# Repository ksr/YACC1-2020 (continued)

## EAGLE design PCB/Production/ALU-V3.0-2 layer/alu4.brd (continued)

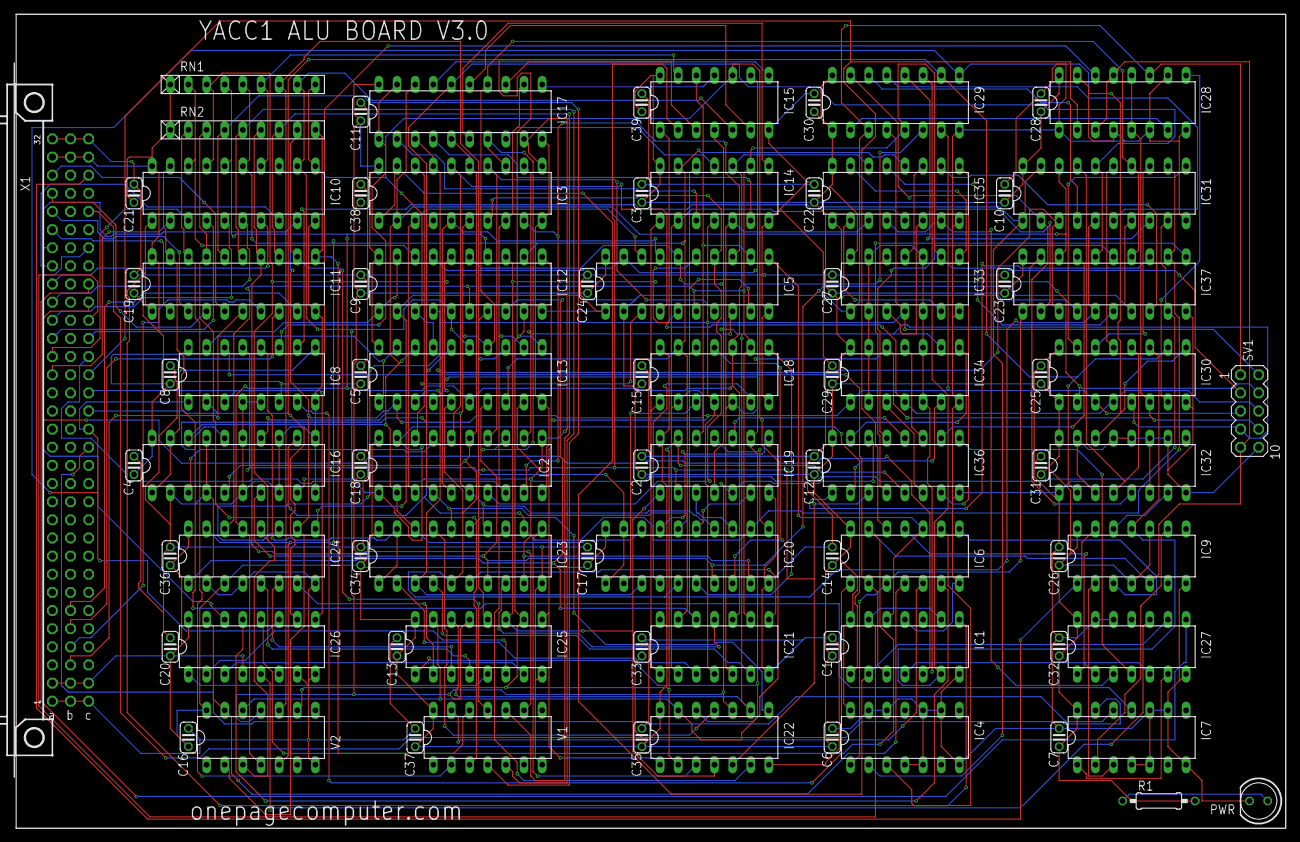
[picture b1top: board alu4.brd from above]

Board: 2 copper layers, 177.8 x 114.0 mm, 84 parts (0 on the bottom side), 158 nets.

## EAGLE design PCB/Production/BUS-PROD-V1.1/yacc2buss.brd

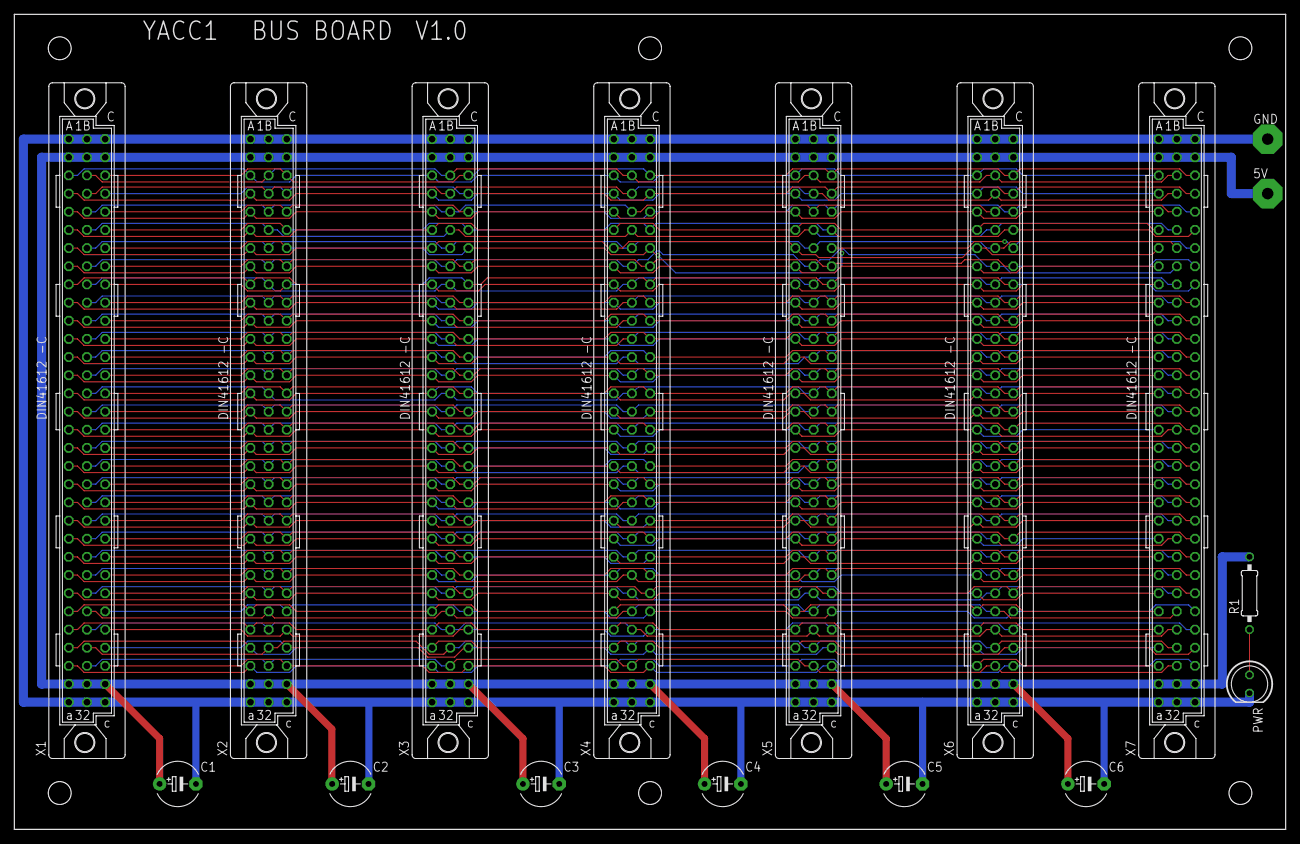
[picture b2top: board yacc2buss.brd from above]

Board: 2 copper layers, 177.8 x 114.0 mm, 17 parts (0 on the bottom side), 87 nets.

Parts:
5V: WIREPAD4,16O1,6; 4,16O1,6
C1, C2, C3, C4, C5, C6: E5-6
GND: WIREPAD4,16O1,6; 4,16O1,6
PWR: LED5MM
R1: 330; 0207/10
X1, X2, X3, X4, X5, X6, X7: FABC96S

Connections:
5V: 5V.1, C1.+, C2.+, C3.+, C4.+, C5.+, C6.+, R1.2, X1.A2, X1.A31, X1.B2, X1.B31, X1.C2, X1.C31, X2.A2, X2.A31, X2.B2, X2.B31, X2.C2, X2.C31, X3.A2, X3.A31, X3.B2, X3.B31, X3.C2, X3.C31, X4.A2, X4.A31, X4.B2, X4.B31, X4.C2, X4.C31, X5.A2, X5.A31, X5.B2, X5.B31, X5.C2, X5.C31, X6.A2, X6.A31, X6.B2, X6.B31, X6.C2, X6.C31, X7.A2, X7.A31, X7.B2, X7.B31, X7.C2, X7.C31
GND: C1.-, C2.-, C3.-, C4.-, C5.-, C6.-, GND.1, PWR.K, X1.A1, X1.A32, X1.B1, X1.B32, X1.C1, X1.C32, X2.A1, X2.A32, X2.B1, X2.B32, X2.C1, X2.C32, X3.A1, X3.A32, X3.B1, X3.B32, X3.C1, X3.C32, X4.A1, X4.A32, X4.B1, X4.B32, X4.C1, X4.C32, X5.A1, X5.A32, X5.B1, X5.B32, X5.C1, X5.C32, X6.A1, X6.A32, X6.B1, X6.B32, X6.C1, X6.C32, X7.A1, X7.A32, X7.B1, X7.B32, X7.C1, X7.C32
unnamed: PWR.A, R1.1
SIG0: X1.A4, X2.A4, X3.A4, X4.A4, X5.A4, X6.A4, X7.A4
SIG1: X1.B4, X2.B4, X3.B4, X4.B4, X5.B4, X6.B4, X7.B4
SIG2: X1.C4, X2.C4, X3.C4, X4.C4, X5.C4, X6.C4, X7.C4
SIG3: X1.A5, X2.A5, X3.A5, X4.A5, X5.A5, X6.A5, X7.A5
SIG4: X1.B5, X2.B5, X3.B5, X4.B5, X5.B5, X6.B5, X7.B5
SIG5: X1.C5, X2.C5, X3.C5, X4.C5, X5.C5, X6.C5, X7.C5
SIG6: X1.A6, X2.A6, X3.A6, X4.A6, X5.A6, X6.A6, X7.A6
SIG7: X1.B6, X2.B6, X3.B6, X4.B6, X5.B6, X6.B6, X7.B6
SIG8: X1.C6, X2.C6, X3.C6, X4.C6, X5.C6, X6.C6, X7.C6
SIG9: X1.A7, X2.A7, X3.A7, X4.A7, X5.A7, X6.A7, X7.A7
SIG10: X1.B7, X2.B7, X3.B7, X4.B7, X5.B7, X6.B7, X7.B7
SIG11: X1.C7, X2.C7, X3.C7, X4.C7, X5.C7, X6.C7, X7.C7
SIG12: X1.A8, X2.A8, X3.A8, X4.A8, X5.A8, X6.A8, X7.A8
SIG13: X1.B8, X2.B8, X3.B8, X4.B8, X5.B8, X6.B8, X7.B8
SIG14: X1.C8, X2.C8, X3.C8, X4.C8, X5.C8, X6.C8, X7.C8
SIG15: X1.A9, X2.A9, X3.A9, X4.A9, X5.A9, X6.A9, X7.A9
SIG16: X1.B9, X2.B9, X3.B9, X4.B9, X5.B9, X6.B9, X7.B9
SIG17: X1.C9, X2.C9, X3.C9, X4.C9, X5.C9, X6.C9, X7.C9
SIG18: X1.A10, X2.A10, X3.A10, X4.A10, X5.A10, X6.A10, X7.A10
SIG19: X1.B10, X2.B10, X3.B10, X4.B10, X5.B10, X6.B10, X7.B10
SIG20: X1.C10, X2.C10, X3.C10, X4.C10, X5.C10, X6.C10, X7.C10
SIG21: X1.A11, X2.A11, X3.A11, X4.A11, X5.A11, X6.A11, X7.A11
SIG22: X1.B11, X2.B11, X3.B11, X4.B11, X5.B11, X6.B11, X7.B11
SIG23: X1.C11, X2.C11, X3.C11, X4.C11, X5.C11, X6.C11, X7.C11
SIG24: X1.A12, X2.A12, X3.A12, X4.A12, X5.A12, X6.A12, X7.A12
SIG25: X1.B12, X2.B12, X3.B12, X4.B12, X5.B12, X6.B12, X7.B12
SIG26: X1.C12, X2.C12, X3.C12, X4.C12, X5.C12, X6.C12, X7.C12
SIG27: X1.A13, X2.A13, X3.A13, X4.A13, X5.A13, X6.A13, X7.A13
SIG28: X1.B13, X2.B13, X3.B13, X4.B13, X5.B13, X6.B13, X7.B13
SIG29: X1.C13, X2.C13, X3.C13, X4.C13, X5.C13, X6.C13, X7.C13
SIG30: X1.A14, X2.A14, X3.A14, X4.A14, X5.A14, X6.A14, X7.A14
SIG31: X1.B14, X2.B14, X3.B14, X4.B14, X5.B14, X6.B14, X7.B14
SIG32: X1.C14, X2.C14, X3.C14, X4.C14, X5.C14, X6.C14, X7.C14
SIG33: X1.A15, X2.A15, X3.A15, X4.A15, X5.A15, X6.A15, X7.A15
SIG34: X1.B15, X2.B15, X3.B15, X4.B15, X5.B15, X6.B15, X7.B15
SIG35: X1.C15, X2.C15, X3.C15, X4.C15, X5.C15, X6.C15, X7.C15
SIG36: X1.A16, X2.A16, X3.A16, X4.A16, X5.A16, X6.A16, X7.A16
SIG37: X1.B16, X2.B16, X3.B16, X4.B16, X5.B16, X6.B16, X7.B16
SIG38: X1.C16, X2.C16, X3.C16, X4.C16, X5.C16, X6.C16, X7.C16
SIG39: X1.A17, X2.A17, X3.A17, X4.A17, X5.A17, X6.A17, X7.A17
SIG40: X1.B17, X2.B17, X3.B17, X4.B17, X5.B17, X6.B17, X7.B17
SIG41: X1.C17, X2.C17, X3.C17, X4.C17, X5.C17, X6.C17, X7.C17
SIG42: X1.A18, X2.A18, X3.A18, X4.A18, X5.A18, X6.A18, X7.A18
SIG43: X1.B18, X2.B18, X3.B18, X4.B18, X5.B18, X6.B18, X7.B18
SIG44: X1.C18, X2.C18, X3.C18, X4.C18, X5.C18, X6.C18, X7.C18
SIG45: X1.A19, X2.A19, X3.A19, X4.A19, X5.A19, X6.A19, X7.A19
SIG46: X1.B19, X2.B19, X3.B19, X4.B19, X5.B19, X6.B19, X7.B19
SIG47: X1.C19, X2.C19, X3.C19, X4.C19, X5.C19, X6.C19, X7.C19
SIG48: X1.A20, X2.A20, X3.A20, X4.A20, X5.A20, X6.A20, X7.A20
SIG49: X1.B20, X2.B20, X3.B20, X4.B20, X5.B20, X6.B20, X7.B20
SIG50: X1.C20, X2.C20, X3.C20, X4.C20, X5.C20, X6.C20, X7.C20
SIG51: X1.A21, X2.A21, X3.A21, X4.A21, X5.A21, X6.A21, X7.A21
SIG52: X1.B21, X2.B21, X3.B21, X4.B21, X5.B21, X6.B21, X7.B21
SIG53: X1.C21, X2.C21, X3.C21, X4.C21, X5.C21, X6.C21, X7.C21
SIG54: X1.A22, X2.A22, X3.A22, X4.A22, X5.A22, X6.A22, X7.A22
SIG55: X1.B22, X2.B22, X3.B22, X4.B22, X5.B22, X6.B22, X7.B22
SIG56: X1.C22, X2.C22, X3.C22, X4.C22, X5.C22, X6.C22, X7.C22
SIG57: X1.A23, X2.A23, X3.A23, X4.A23, X5.A23, X6.A23, X7.A23
SIG58: X1.B23, X2.B23, X3.B23, X4.B23, X5.B23, X6.B23, X7.B23
SIG59: X1.C23, X2.C23, X3.C23, X4.C23, X5.C23, X6.C23, X7.C23
SIG60: X1.A24, X2.A24, X3.A24, X4.A24, X5.A24, X6.A24, X7.A24
SIG61: X1.B24, X2.B24, X3.B24, X4.B24, X5.B24, X6.B24, X7.B24
SIG62: X1.C24, X2.C24, X3.C24, X4.C24, X5.C24, X6.C24, X7.C24
SIG63: X1.A25, X2.A25, X3.A25, X4.A25, X5.A25, X6.A25, X7.A25
SIG64: X1.B25, X2.B25, X3.B25, X4.B25, X5.B25, X6.B25, X7.B25
SIG65: X1.C25, X2.C25, X3.C25, X4.C25, X5.C25, X6.C25, X7.C25
SIG66: X1.A26, X2.A26, X3.A26, X4.A26, X5.A26, X6.A26, X7.A26
SIG67: X1.B26, X2.B26, X3.B26, X4.B26, X5.B26, X6.B26, X7.B26
SIG68: X1.C26, X2.C26, X3.C26, X4.C26, X5.C26, X6.C26, X7.C26
SIG69: X1.A27, X2.A27, X3.A27, X4.A27, X5.A27, X6.A27, X7.A27
SIG70: X1.B27, X2.B27, X3.B27, X4.B27, X5.B27, X6.B27, X7.B27
SIG71: X1.C27, X2.C27, X3.C27, X4.C27, X5.C27, X6.C27, X7.C27
SIG72: X1.A28, X2.A28, X3.A28, X4.A28, X5.A28, X6.A28, X7.A28
SIG73: X1.B28, X2.B28, X3.B28, X4.B28, X5.B28, X6.B28, X7.B28
SIG74: X1.C28, X2.C28, X3.C28, X4.C28, X5.C28, X6.C28, X7.C28
SIG75: X1.A29, X2.A29, X3.A29, X4.A29, X5.A29, X6.A29, X7.A29
SIG76: X1.B29, X2.B29, X3.B29, X4.B29, X5.B29, X6.B29, X7.B29
SIG77: X1.C29, X2.C29, X3.C29, X4.C29, X5.C29, X6.C29, X7.C29
SIG78: X1.A30, X2.A30, X3.A30, X4.A30, X5.A30, X6.A30, X7.A30
SIG79: X1.B30, X2.B30, X3.B30, X4.B30, X5.B30, X6.B30, X7.B30
SIG80: X1.C30, X2.C30, X3.C30, X4.C30, X5.C30, X6.C30, X7.C30
SIG81: X1.A3, X2.A3, X3.A3, X4.A3, X5.A3, X6.A3, X7.A3
SIG82: X1.B3, X2.B3, X3.B3, X4.B3, X5.B3, X6.B3, X7.B3
SIG83: X1.C3, X2.C3, X3.C3, X4.C3, X5.C3, X6.C3, X7.C3

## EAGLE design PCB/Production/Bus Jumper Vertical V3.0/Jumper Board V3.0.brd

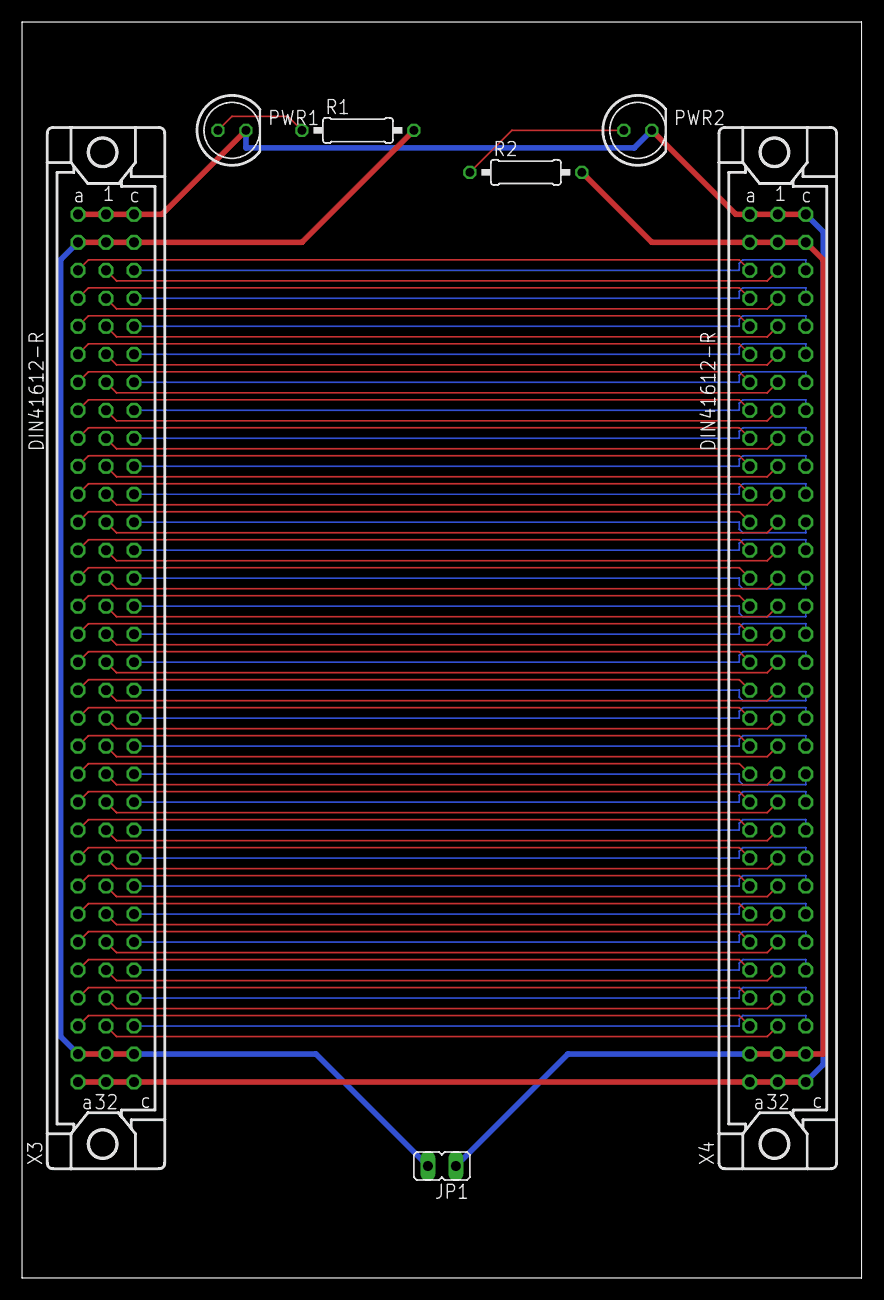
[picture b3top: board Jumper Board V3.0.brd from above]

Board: 2 copper layers, 76.2 x 114.0 mm, 7 parts (0 on the bottom side), 89 nets.

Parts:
JP1: JP1
PWR1, PWR2: LED5MM
R1, R2: 330; 0207/10
X3, X4: MABC96R

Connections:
GND: PWR1.K, PWR2.K, X3.A1, X3.A32, X3.B1, X3.B32, X3.C1, X3.C32, X4.A1, X4.A32, X4.B1, X4.B32, X4.C1, X4.C32
unnamed: X3.A3, X4.A3
unnamed: X3.A4, X4.A4
unnamed: X3.A5, X4.A5
unnamed: X3.A6, X4.A6
unnamed: X3.A7, X4.A7
unnamed: X3.A8, X4.A8
unnamed: X3.A9, X4.A9
unnamed: X3.A10, X4.A10
unnamed: X3.A11, X4.A11
unnamed: X3.A12, X4.A12
unnamed: X3.A13, X4.A13
unnamed: X3.A14, X4.A14
unnamed: X3.A15, X4.A15
unnamed: X3.A16, X4.A16
unnamed: X3.A17, X4.A17
unnamed: X3.A18, X4.A18
unnamed: X3.A19, X4.A19
unnamed: X3.A20, X4.A20
unnamed: X3.A21, X4.A21
unnamed: X3.A22, X4.A22
unnamed: X3.A23, X4.A23
unnamed: X3.A24, X4.A24
unnamed: X3.A25, X4.A25
unnamed: X3.A26, X4.A26
unnamed: X3.A27, X4.A27
unnamed: X3.A28, X4.A28
unnamed: X3.A29, X4.A29
unnamed: X3.A30, X4.A30
unnamed: PWR1.A, R1.1
unnamed: PWR2.A, R2.1
unnamed: X3.B3, X4.B3
unnamed: X3.B4, X4.B4
unnamed: X3.B5, X4.B5
unnamed: X3.B6, X4.B6
unnamed: X3.B7, X4.B7
unnamed: X3.B8, X4.B8
unnamed: X3.B9, X4.B9
unnamed: X3.B10, X4.B10
unnamed: X3.B11, X4.B11
unnamed: X3.B12, X4.B12
unnamed: X3.B13, X4.B13
unnamed: X3.B14, X4.B14
unnamed: X3.B15, X4.B15
unnamed: X3.B16, X4.B16
unnamed: X3.B17, X4.B17
unnamed: X3.B18, X4.B18
unnamed: X3.B19, X4.B19
unnamed: X3.B20, X4.B20
unnamed: X3.B21, X4.B21
unnamed: X3.B22, X4.B22
unnamed: X3.B23, X4.B23
unnamed: X3.B24, X4.B24
unnamed: X3.B25, X4.B25
unnamed: X3.B26, X4.B26
unnamed: X3.B27, X4.B27
unnamed: X3.B28, X4.B28
unnamed: X3.B29, X4.B29
unnamed: X3.B30, X4.B30
unnamed: X3.C3, X4.C3
unnamed: X3.C4, X4.C4
unnamed: X3.C5, X4.C5
unnamed: X3.C6, X4.C6
unnamed: X3.C7, X4.C7
unnamed: X3.C8, X4.C8
unnamed: X3.C9, X4.C9
unnamed: X3.C10, X4.C10
unnamed: X3.C11, X4.C11
unnamed: X3.C12, X4.C12
unnamed: X3.C13, X4.C13
unnamed: X3.C14, X4.C14
unnamed: X3.C15, X4.C15
unnamed: X3.C16, X4.C16
unnamed: X3.C17, X4.C17
unnamed: X3.C18, X4.C18
unnamed: X3.C19, X4.C19
unnamed: X3.C20, X4.C20
unnamed: X3.C21, X4.C21
unnamed: X3.C22, X4.C22
unnamed: X3.C23, X4.C23
unnamed: X3.C24, X4.C24
unnamed: X3.C25, X4.C25
unnamed: X3.C26, X4.C26
unnamed: X3.C27, X4.C27
unnamed: X3.C28, X4.C28
unnamed: X3.C29, X4.C29
unnamed: X3.C30, X4.C30
V1: JP1.2, R1.2, X3.A2, X3.A31, X3.B2, X3.B31, X3.C2, X3.C31
V2: JP1.1, R2.2, X4.A2, X4.A31, X4.B2, X4.B31, X4.C2, X4.C31

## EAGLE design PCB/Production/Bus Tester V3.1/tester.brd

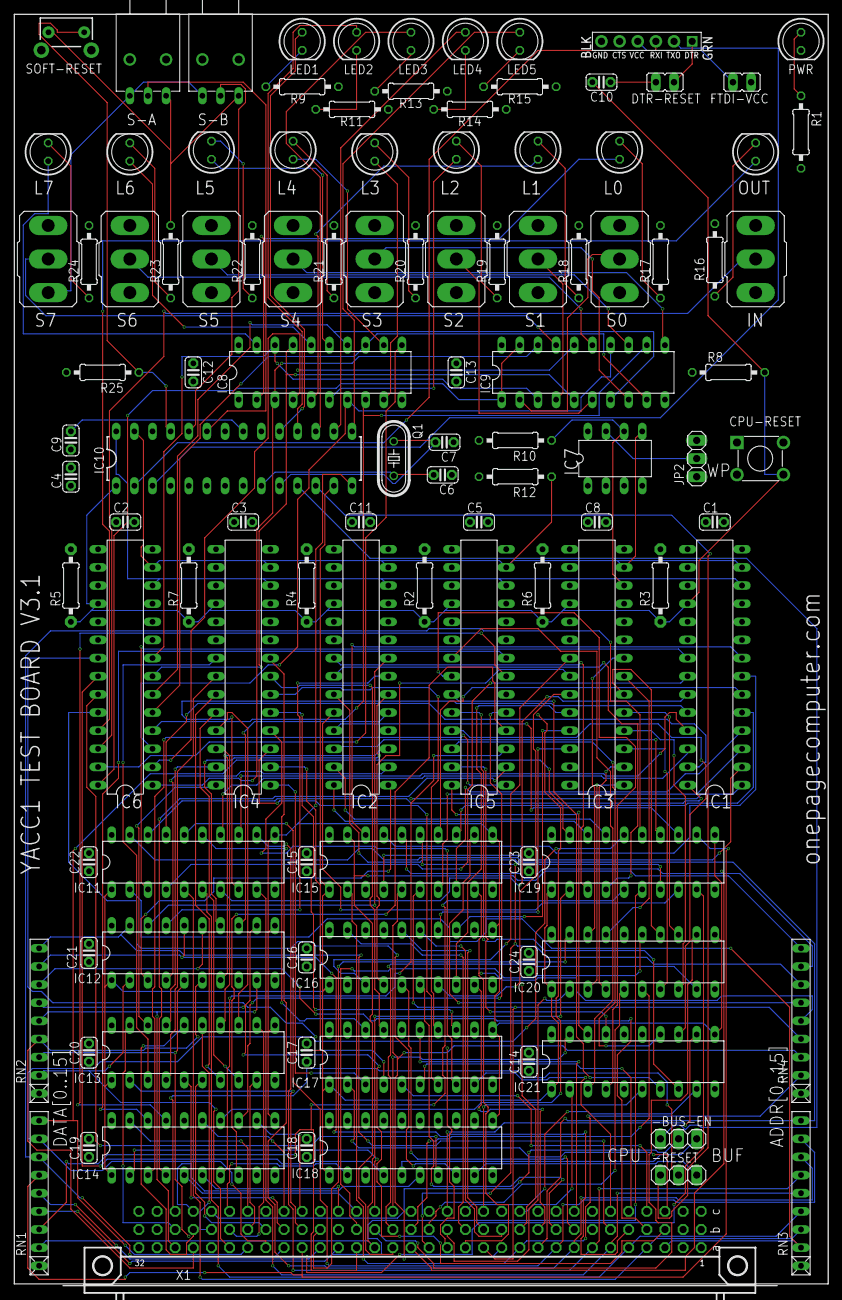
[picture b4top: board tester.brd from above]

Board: 4 copper layers, 114.0 x 177.8 mm, 110 parts (0 on the bottom side), 239 nets.

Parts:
-BUS-EN: 1X03
-RESET: 1X03
C1, C2, C3, C4, C5, C8, C9, C10, C11, C12, C13, C14, C15, C16, C17, C18, C19, C20, C21, C22, C23, C24: 0.1; C025-024X044
C6, C7: 20pf; C025-024X044
CPU-RESET: TS-1109-7; SW4-6.2X6.2X5.0MM
DTR-RESET: JP1
FTDI-VCC: JP1
IC1, IC2, IC3, IC4, IC5, IC6: MCP23017SP; DIL28-3
IC7: 24AA01P; DIL8
IC8: 74LS374N; DIL20
IC9: 74LS244N; DIL20
IC10: ATMEGA328P_PDIP; DIL28-3
IC11, IC12, IC13, IC14, IC15, IC16, IC17, IC18, IC19, IC20, IC21: 74LS373N; DIL20
IN: M9040P
JP1: FTDI_DEVICE; FTDI_DEVICE_SIDE
JP2: 1X03
L0, L1, L2, L3, L4, L5, L6, L7: LED5MM
LED1, LED2, LED3, LED4, LED5: LED5MM
OUT: LED5MM
PWR: LED5MM
Q1: 16Mhz; HC49/S
R1, R9, R11, R13, R14, R15, R16, R17, R18, R19, R20, R21, R22, R23, R24: 330; 0207/10
R2, R3, R4, R5, R6, R7, R8, R25: 10k; 0207/10
R10, R12: 2.2k; 0207/10
RN1, RN2, RN3, RN4: RN-9
S0, S1, S2, S3, S4, S5, S6, S7: M9040P
S-A: 9070-1W
S-B: 9070-1W
SOFT-RESET: SWITCH-MOMENTARY-2SIDE_EZ; TACTILE-PTH-SIDEEZ
X1: FABC96R

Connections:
-BUF-EN: IC10.13, IC11.1, IC12.1, IC13.1, IC14.1, IC15.1, IC16.1, IC17.1, IC18.1, IC19.1, IC20.1, IC21.1
-RESET: C10.2, CPU-RESET.3, IC1.18, IC2.18, IC3.18, IC4.18, IC5.18, IC6.18, IC10.1, R2.1, R3.1, R4.1, R5.1, R6.1, R7.1, R8.2
-SOFT-BUS-EN: -BUS-EN.1, IC10.11
-SOFT-RESET: -RESET.1, IC10.12
A3: IC11.2, RN3.2, X1.A3
A4: IC11.5, RN3.3, X1.A4
A5: IC11.6, RN3.4, X1.A5
A6: IC11.9, RN3.5, X1.A6
A7: IC11.12, RN3.6, X1.A7
A8: IC11.15, RN3.7, X1.A8
A9: IC11.16, RN3.8, X1.A9
A10: IC11.19, RN3.9, X1.A10
A11: IC15.2, RN4.2, X1.A11
A12: IC15.5, RN4.3, X1.A12
A13: IC15.6, RN4.4, X1.A13
A14: IC15.9, RN4.5, X1.A14
A15: IC15.12, RN4.6, X1.A15
A16: IC15.15, RN4.7, X1.A16
A17: IC15.16, RN4.8, X1.A17
A18: IC15.19, RN4.9, X1.A18
A19: IC19.2, RN1.2, X1.A19
A20: IC19.5, RN1.3, X1.A20
A21: IC19.6, RN1.4, X1.A21
A22: IC19.9, RN1.5, X1.A22
A23: IC19.12, RN1.6, X1.A23
A24: IC19.15, RN1.7, X1.A24
A25: IC19.16, RN1.8, X1.A25
A26: IC19.19, RN1.9, X1.A26
A27: IC12.2, RN2.2, X1.A27
A28: IC12.5, RN2.3, X1.A28
A29: IC12.6, RN2.4, X1.A29
A30: IC12.9, RN2.5, X1.A30
ARD-RXIN: IC10.2, JP1.P$3
ARD-TXOUT: IC10.3, JP1.P$2
B3: IC12.12, RN2.6, X1.B3
B4: IC12.15, RN2.7, X1.B4
B5: IC12.16, RN2.8, X1.B5
B6: IC12.19, RN2.9, X1.B6
B7: IC16.2, X1.B7
B8: IC16.5, X1.B8
B9: IC16.6, X1.B9
B10: IC16.9, X1.B10
B11: IC16.12, X1.B11
B12: IC16.15, X1.B12
B13: IC16.16, X1.B13
B14: IC16.19, X1.B14
B15: IC20.2, X1.B15
B16: IC20.5, X1.B16
B17: IC20.6, X1.B17
B18: IC20.9, X1.B18
B19: IC20.12, X1.B19
B20: IC20.15, X1.B20
B21: IC20.16, X1.B21
B22: IC20.19, X1.B22
B23: IC13.2, X1.B23
B24: IC13.5, X1.B24
B25: IC13.6, X1.B25
B26: IC13.9, X1.B26
B27: IC13.12, X1.B27
B28: IC13.15, X1.B28
B29: IC13.16, X1.B29
B30: IC13.19, X1.B30
BIT0: IC6.1, IC8.3, IC9.18
BIT1: IC6.2, IC8.4, IC9.16
BIT2: IC6.3, IC8.7, IC9.14
BIT3: IC6.4, IC8.8, IC9.12
BIT4: IC6.5, IC8.13, IC9.9
BIT5: IC6.6, IC8.14, IC9.7
BIT6: IC6.7, IC8.17, IC9.5
BIT7: IC6.8, IC8.18, IC9.3
BUF-A3: IC1.21, IC11.3
BUF-A4: IC1.22, IC11.4
BUF-A5: IC1.23, IC11.7
BUF-A6: IC1.24, IC11.8
BUF-A7: IC1.25, IC11.13
BUF-A8: IC1.26, IC11.14
BUF-A9: IC1.27, IC11.17
BUF-A10: IC1.28, IC11.18
BUF-A11: IC1.1, IC15.3
BUF-A12: IC1.2, IC15.4
BUF-A13: IC1.3, IC15.7
BUF-A14: IC1.4, IC15.8
BUF-A15: IC1.5, IC15.13
BUF-A16: IC1.6, IC15.14
BUF-A17: IC1.7, IC15.17
BUF-A18: IC1.8, IC15.18
BUF-A19: IC2.21, IC19.3
BUF-A20: IC2.22, IC19.4
BUF-A21: IC2.23, IC19.7
BUF-A22: IC2.24, IC19.8
BUF-A23: IC2.25, IC19.13
BUF-A24: IC2.26, IC19.14
BUF-A25: IC2.27, IC19.17
BUF-A26: IC2.28, IC19.18
BUF-A27: IC2.1, IC12.3
BUF-A28: IC2.2, IC12.4
BUF-A29: IC2.3, IC12.7
BUF-A30: IC2.4, IC12.8
BUF-B3: IC2.5, IC12.13
BUF-B4: IC2.6, IC12.14
BUF-B5: IC2.7, IC12.17
BUF-B6: IC2.8, IC12.18
BUF-B7: IC3.21, IC16.3
BUF-B8: IC3.22, IC16.4
BUF-B9: IC3.23, IC16.7
BUF-B10: IC3.24, IC16.8
BUF-B11: IC3.25, IC16.13
BUF-B12: IC3.26, IC16.14
BUF-B13: IC3.27, IC16.17
BUF-B14: IC3.28, IC16.18
BUF-B15: IC3.1, IC20.3
BUF-B16: IC3.2, IC20.4
BUF-B17: IC3.3, IC20.7
BUF-B18: IC3.4, IC20.8
BUF-B19: IC3.5, IC20.13
BUF-B20: IC3.6, IC20.14
BUF-B21: IC3.7, IC20.17
BUF-B22: IC3.8, IC20.18
BUF-B23: IC4.21, IC13.3
BUF-B24: IC4.22, IC13.4
BUF-B25: IC4.23, IC13.7
BUF-B26: IC4.24, IC13.8
BUF-B27: IC4.25, IC13.13
BUF-B28: IC4.26, IC13.14
BUF-B29: IC4.27, IC13.17
BUF-B30: IC4.28, IC13.18
BUF-C3: IC4.1, IC17.3
BUF-C4: IC4.2, IC17.4
BUF-C5: IC4.3, IC17.7
BUF-C6: IC4.4, IC17.8
BUF-C7: IC4.5, IC17.13
BUF-C8: IC4.6, IC17.14
BUF-C9: IC4.7, IC17.17
BUF-C10: IC4.8, IC17.18
BUF-C11: IC5.21, IC21.3
BUF-C12: IC5.22, IC21.4
BUF-C13: IC5.23, IC21.7
BUF-C14: IC5.24, IC21.8
BUF-C15: IC5.25, IC21.13
BUF-C16: IC5.26, IC21.14
BUF-C17: IC5.27, IC21.17
BUF-C18: IC5.28, IC21.18
BUF-C19: IC5.1, IC14.3
BUF-C20: IC5.2, IC14.4
BUF-C21: IC5.3, IC14.7
BUF-C22: IC5.4, IC14.8
BUF-C23: IC5.5, IC14.13
BUF-C24: IC5.6, IC14.14
BUF-C25: IC5.7, IC14.17
BUF-C26: IC5.8, IC14.18
BUF-C27: IC6.21, IC18.3
BUF-C28: IC6.22, IC18.4
BUF-C29: IC6.23, IC18.7
BUF-C30: IC6.24, IC18.8
BUF-CLK: IC10.14, IC11.11, IC12.11, IC13.11, IC14.11, IC15.11, IC16.11, IC17.11, IC18.11, IC19.11, IC20.11, IC21.11
C3: IC17.2, X1.C3
C4: IC17.5, X1.C4
C5: IC17.6, X1.C5
C6: IC17.9, X1.C6
C7: IC17.12, X1.C7
C8: IC17.15, X1.C8
C9: IC17.16, X1.C9
C10: IC17.19, X1.C10
C11: IC21.2, X1.C11
C12: IC21.5, X1.C12
C13: IC21.6, X1.C13
C14: IC21.9, X1.C14
C15: IC21.12, X1.C15
C16: IC21.15, X1.C16
C17: IC21.16, X1.C17
C18: IC21.19, X1.C18
C19: IC14.2, X1.C19
C20: IC14.5, X1.C20
C21: IC14.6, X1.C21
C22: IC14.9, X1.C22
C23: IC14.12, X1.C23
C24: IC14.15, X1.C24
C25: IC14.16, X1.C25
C26: IC14.19, X1.C26
C27: IC18.2, X1.C27
C28: -BUS-EN.2, X1.C28
C29: IC18.6, X1.C29
C30: -RESET.2, X1.C30
GND: C1.1, C2.1, C3.1, C4.1, C5.1, C6.1, C7.1, C8.1, C9.1, C11.1, C12.1, C13.1, C14.1, C15.1, C16.1, C17.1, C18.1, C19.1, C20.1, C21.1, C22.1, C23.1, C24.1, CPU-RESET.1, IC1.10, IC1.15, IC1.16, IC1.17, IC2.10, IC2.16, IC2.17, IC3.10, IC3.15, IC3.17, IC4.10, IC4.17, IC5.10, IC5.15, IC5.16, IC6.10, IC6.16, IC7.4, IC8.1, IC8.10, IC9.10, IC10.8, IC10.22, IC11.10, IC12.10, IC13.10, IC14.10, IC15.10, IC16.10, IC17.10, IC18.10, IC18.13, IC18.14, IC18.17, IC18.18, IC19.10, IC20.10, IC21.10, IN.3, JP1.P$5, JP1.P$6, JP2.1, PWR.K, R9.2, R11.2, R13.2, R14.2, R15.2, R16.2, R17.2, R18.2, R19.2, R20.2, R21.2, R22.2, R23.2, R24.2, S0.3, S1.3, S2.3, S3.3, S4.3, S5.3, S6.3, S7.3, S-A.3, S-B.3, SOFT-RESET.2, X1.A1, X1.A32, X1.B1, X1.B32, X1.C1, X1.C32
IN-SWITCH: IC6.26, IN.2
LEDS-LD: IC6.27, IC8.11
unnamed: IC10.19, LED1.A
unnamed: IC7.7, JP2.2
unnamed: C6.2, IC10.9, Q1.2
unnamed: C7.2, IC10.10, Q1.1
unnamed: PWR.A, R1.1
unnamed: IC10.18, LED2.A
unnamed: IC10.17, LED3.A
unnamed: IC10.16, LED4.A
unnamed: C10.1, DTR-RESET.2
unnamed: IC10.15, LED5.A
unnamed: LED2.K, R11.1
unnamed: LED1.K, R9.1
unnamed: LED3.K, R13.1
unnamed: C9.2, IC10.21
unnamed: LED4.K, R14.1
unnamed: LED5.K, R15.1
unnamed: L7.K, R24.1
unnamed: IC10.23, S-A.2
unnamed: IC10.24, S-B.2
unnamed: L6.K, R23.1
unnamed: L5.K, R22.1
unnamed: L4.K, R21.1
unnamed: L3.K, R20.1
unnamed: L2.K, R19.1
unnamed: L1.K, R18.1
unnamed: L0.K, R17.1
unnamed: OUT.K, R16.1
unnamed: DTR-RESET.1, JP1.P$1
unnamed: FTDI-VCC.2, JP1.P$4
unnamed: -BUS-EN.3, IC18.5
unnamed: IC8.5, L1.A
unnamed: IC8.9, L3.A
unnamed: IC8.12, L4.A
unnamed: IC8.15, L5.A
unnamed: IC8.6, L2.A
unnamed: IC8.16, L6.A
unnamed: IC8.19, L7.A
unnamed: IC8.2, L0.A
unnamed: IC10.25, R25.1, SOFT-RESET.1
unnamed: IC9.2, S0.2
unnamed: IC9.8, S3.2
unnamed: IC9.6, S2.2
unnamed: IC9.4, S1.2
unnamed: IC9.11, S4.2
unnamed: IC9.17, S7.2
unnamed: IC9.13, S5.2
unnamed: IC9.15, S6.2
unnamed: -RESET.3, IC18.9
OUT-LED: IC6.25, OUT.A
SCL: IC1.12, IC2.12, IC3.12, IC4.12, IC5.12, IC6.12, IC7.6, IC10.28, R10.1
SDA: IC1.13, IC2.13, IC3.13, IC4.13, IC5.13, IC6.13, IC7.5, IC10.27, R12.1
SWITCHES-RD: IC6.28, IC9.1, IC9.19
VCC: C1.2, C2.2, C3.2, C4.2, C5.2, C8.2, C11.2, C12.2, C13.2, C14.2, C15.2, C16.2, C17.2, C18.2, C19.2, C20.2, C21.2, C22.2, C23.2, C24.2, FTDI-VCC.1, IC1.9, IC2.9, IC2.15, IC3.9, IC3.16, IC4.9, IC4.15, IC4.16, IC5.9, IC5.17, IC6.9, IC6.15, IC6.17, IC7.1, IC7.2, IC7.3, IC7.8, IC8.20, IC9.20, IC10.7, IC10.20, IC11.20, IC12.20, IC13.20, IC14.20, IC15.20, IC16.20, IC17.20, IC18.20, IC19.20, IC20.20, IC21.20, IN.1, JP2.3, R1.2, R2.2, R3.2, R4.2, R5.2, R6.2, R7.2, R8.1, R10.2, R12.2, R25.2, RN1.1, RN2.1, RN3.1, RN4.1, S0.1, S1.1, S2.1, S3.1, S4.1, S5.1, S6.1, S7.1, S-A.1, S-B.1, X1.A2, X1.A31, X1.B2, X1.B31, X1.C2, X1.C31

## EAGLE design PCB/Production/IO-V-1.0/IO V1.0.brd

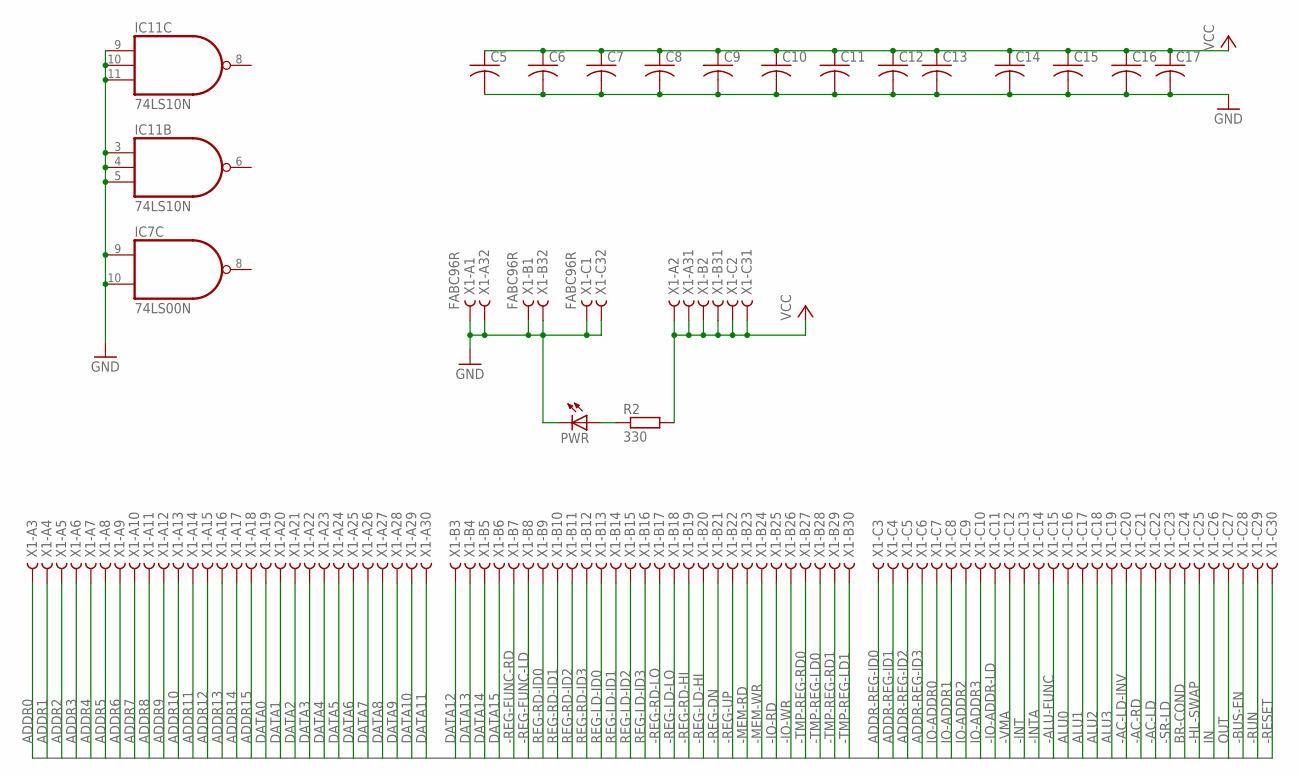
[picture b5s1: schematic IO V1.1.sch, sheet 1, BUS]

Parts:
C5, C6, C7, C8, C9, C10, C11, C12, C13, C14, C15, C16, C17: C-US025-024X044; C025-024X044
IC7: 74LS00N; DIL14
IC11: 74LS10N; DIL14
PWR: LED5MM
R2: 330; 0207/10
X1: FABC96R

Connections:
-AC-LD: X1.C22
-AC-LD-INV: X1.C20
-AC-RD: X1.C21
-ADDR-REG-LD0: X1.C4
-ADDR-REG-LD1: X1.C6
-ADDR-REG-RD0: X1.C3
-ADDR-REG-RD1: X1.C5
-ALU-FUNC: X1.C15
-BUS-EN: X1.C28
-HL-SWAP: X1.C25
-INT: X1.C13; also elsewhere on the board
-INTA: X1.C14
-IO-ADDR-LD: X1.C11
-IO-RD: X1.B25; also elsewhere on the board
-IO-WR: X1.B26; also elsewhere on the board
-MEM-RD: X1.B23
-MEM-WR: X1.B24
-REG-DN: X1.B21
-REG-FUNC-LD: X1.B8
-REG-FUNC-RD: X1.B7
-REG-LD-HI: X1.B20
-REG-LD-LO: X1.B18
-REG-RD-HI: X1.B19
-REG-RD-LO: X1.B17
-REG-UP: X1.B22
-RESET: X1.C30; also elsewhere on the board
-RUN: X1.C29
-SR-LD: X1.C23
-TMP-REG-LD0: X1.B28
-TMP-REG-LD1: X1.B30
-TMP-REG-RD0: X1.B27
-TMP-REG-RD1: X1.B29
-VMA: X1.C12
ADDR0: X1.A3
ADDR1: X1.A4
ADDR2: X1.A5
ADDR3: X1.A6
ADDR4: X1.A7
ADDR5: X1.A8
ADDR6: X1.A9
ADDR7: X1.A10
ADDR8: X1.A11
ADDR9: X1.A12
ADDR10: X1.A13
ADDR11: X1.A14
ADDR12: X1.A15
ADDR13: X1.A16
ADDR14: X1.A17
ADDR15: X1.A18
ALU0: X1.C16
ALU1: X1.C17
ALU2: X1.C18
ALU3: X1.C19
BR-COND: X1.C24
DATA0: X1.A19; also elsewhere on the board
DATA1: X1.A20; also elsewhere on the board
DATA2: X1.A21; also elsewhere on the board
DATA3: X1.A22; also elsewhere on the board
DATA4: X1.A23; also elsewhere on the board
DATA5: X1.A24; also elsewhere on the board
DATA6: X1.A25; also elsewhere on the board
DATA7: X1.A26; also elsewhere on the board
DATA8: X1.A27
DATA9: X1.A28
DATA10: X1.A29
DATA11: X1.A30
DATA12: X1.B3
DATA13: X1.B4
DATA14: X1.B5
DATA15: X1.B6
IN: X1.C26; also elsewhere on the board
IO-ADDR0: X1.C7; also elsewhere on the board
IO-ADDR1: X1.C8; also elsewhere on the board
IO-ADDR2: X1.C9; also elsewhere on the board
IO-ADDR3: X1.C10; also elsewhere on the board
unnamed: PWR.A, R2.1
OUT: X1.C27; also elsewhere on the board
REG-LD-ID0: X1.B13
REG-LD-ID1: X1.B14
REG-LD-ID2: X1.B15
REG-LD-ID3: X1.B16
REG-RD-ID0: X1.B9
REG-RD-ID1: X1.B10
REG-RD-ID2: X1.B11
REG-RD-ID3: X1.B12
VCC: C5.1, C6.1, C7.1, C8.1, C9.1, C10.1, C11.1, C12.1, C13.1, C14.1, C15.1, C16.1, C17.1, IC7.14 (VCC), R2.2, X1.A2, X1.A31, X1.B2, X1.B31, X1.C2, X1.C31; also elsewhere on the board

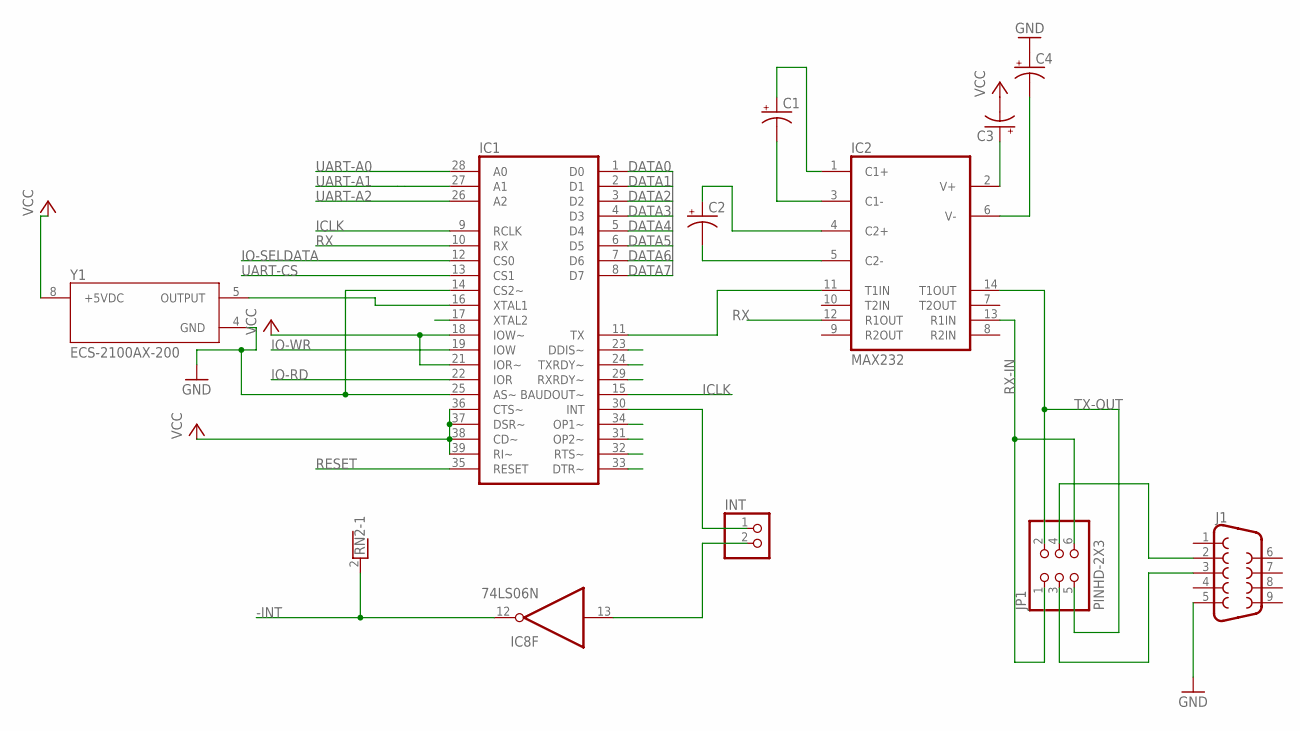
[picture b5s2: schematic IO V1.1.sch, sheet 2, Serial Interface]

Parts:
C1, C2, C3, C4: CPOL-USE2,5-6E; E2,5-6E
IC1: XR-16C550P; DIL40
IC2: MAX232; DIL16
IC8: 74LS06N; DIL14
INT: PINHD-1X2; 1X02
J1: DB9FEMALE; DB9
JP1: PINHD-2X3; 2X03
RN2: RNX6; RN-7
Y1: ECS-2100AX-200

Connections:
-INT: IC8.12 (O), RN2.2; also elsewhere on the board
DATA0: IC1.1 (D0); also elsewhere on the board
DATA1: IC1.2 (D1); also elsewhere on the board
DATA2: IC1.3 (D2); also elsewhere on the board
DATA3: IC1.4 (D3); also elsewhere on the board
DATA4: IC1.5 (D4); also elsewhere on the board
DATA5: IC1.6 (D5); also elsewhere on the board
DATA6: IC1.7 (D6); also elsewhere on the board
DATA7: IC1.8 (D7); also elsewhere on the board
ICLK: IC1.9 (RCLK), IC1.15 (BAUDOUT~)
IO-RD: IC1.22 (IOR); also elsewhere on the board
IO-SELDATA: IC1.12 (CS0); also elsewhere on the board
IO-WR: IC1.19 (IOW); also elsewhere on the board
unnamed: IC1.16 (XTAL1), Y1.5 (OUTPUT)
unnamed 117: J1.9; also elsewhere on the board
unnamed 118: J1.8; also elsewhere on the board
unnamed: IC1.11 (TX), IC2.11 (T1IN)
unnamed 120: J1.7; also elsewhere on the board
unnamed 121: J1.6; also elsewhere on the board
unnamed 123: J1.4; also elsewhere on the board
unnamed 125: J1.3, JP1.3; also elsewhere on the board
unnamed 127: J1.2, JP1.4; also elsewhere on the board
unnamed 128: J1.1; also elsewhere on the board
unnamed 129: IC2.14 (T1OUT), JP1.2, JP1.5; also elsewhere on the board
unnamed 130: IC2.13 (R1IN), JP1.1, JP1.6; also elsewhere on the board
unnamed: C2.-, IC2.5 (C2-)
unnamed: C2.+, IC2.4 (C2+)
unnamed: IC1.30 (INT), INT.1
unnamed: C1.-, IC2.3 (C1-)
unnamed: C1.+, IC2.1 (C1+)
unnamed: C3.+, IC2.2 (V+)
unnamed: C4.-, IC2.6 (V-)
unnamed: IC8.13 (I), INT.2
RESET: IC1.35 (RESET); also elsewhere on the board
RX: IC1.10 (RX), IC2.12 (R1OUT)
UART-A0: IC1.28 (A0); also elsewhere on the board
UART-A1: IC1.27 (A1); also elsewhere on the board
UART-A2: IC1.26 (A2); also elsewhere on the board
UART-CS: IC1.13 (CS1); also elsewhere on the board
VCC: C3.-, IC1.18 (IOW~), IC1.21 (IOR~), IC1.36 (CTS~), IC1.37 (DSR~), IC1.38 (CD~), IC1.39 (RI~), IC1.40 (VCC), IC2.16 (VCC), IC8.14 (VCC), Y1.8 (+5VDC); also elsewhere on the board

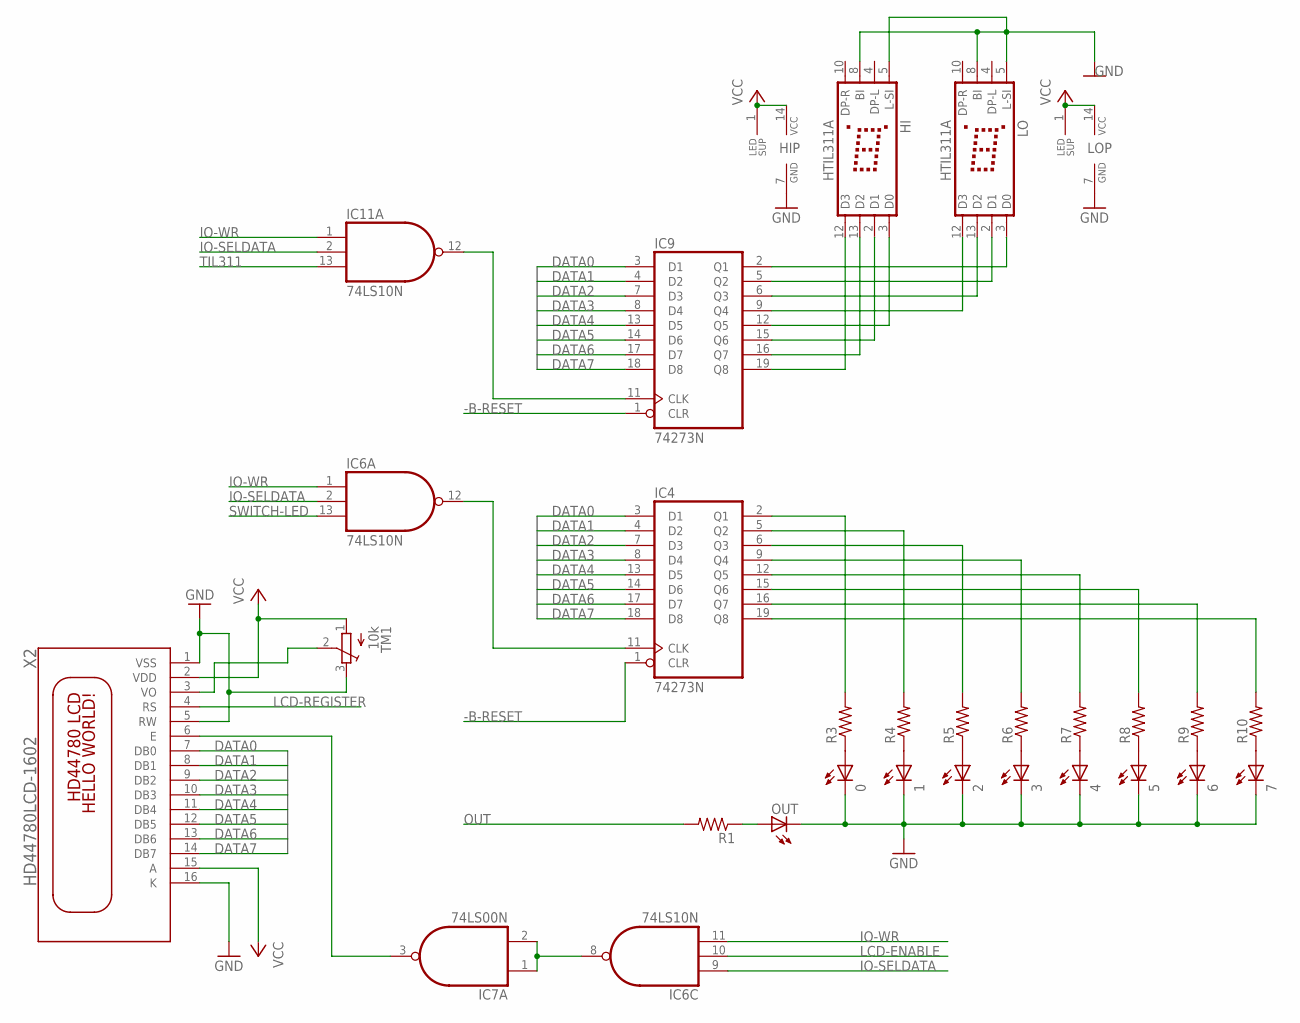
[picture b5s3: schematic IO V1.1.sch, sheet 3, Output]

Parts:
0, 1, 2, 3, 4, 5, 6, 7: LED5MM
HI: HTIL311A
IC4, IC9: 74273N; DIL20
IC6, IC11: 74LS10N; DIL14
IC7: 74LS00N; DIL14
LO: HTIL311A
OUT: LED5MM
R1, R3, R4, R5, R6, R7, R8, R9, R10: R-US_0207/10; 0207/10
TM1: 10k; TRIM-3386
X2: HD44780LCD-1602; LCD1602

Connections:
-B-RESET: IC4.1 (CLR), IC9.1 (CLR); also elsewhere on the board
DATA0: IC4.3 (D1), IC9.3 (D1), X2.7 (DB0); also elsewhere on the board
DATA1: IC4.4 (D2), IC9.4 (D2), X2.8 (DB1); also elsewhere on the board
DATA2: IC4.7 (D3), IC9.7 (D3), X2.9 (DB2); also elsewhere on the board
DATA3: IC4.8 (D4), IC9.8 (D4), X2.10 (DB3); also elsewhere on the board
DATA4: IC4.13 (D5), IC9.13 (D5), X2.11 (DB4); also elsewhere on the board
DATA5: IC4.14 (D6), IC9.14 (D6), X2.12 (DB5); also elsewhere on the board
DATA6: IC4.17 (D7), IC9.17 (D7), X2.13 (DB6); also elsewhere on the board
DATA7: IC4.18 (D8), IC9.18 (D8), X2.14 (DB7); also elsewhere on the board
IO-SELDATA: IC6.2 (I1), IC6.9 (I0), IC11.2 (I1); also elsewhere on the board
IO-WR: IC6.1 (I0), IC6.11 (I2), IC11.1 (I0); also elsewhere on the board
LCD-ENABLE: IC6.10 (I1); also elsewhere on the board
LCD-REGISTER: X2.4 (RS); also elsewhere on the board
unnamed: OUT.A, R1.1
unnamed: 2.A, R5.1
unnamed: 3.A, R6.1
unnamed: 4.A, R7.1
unnamed: 0.A, R3.1
unnamed: 1.A, R4.1
unnamed: 5.A, R8.1
unnamed: 7.A, R10.1
unnamed: 6.A, R9.1
unnamed: IC7.3 (O), X2.6 (E)
unnamed: IC6.8 (O), IC7.1 (I0), IC7.2 (I1)
unnamed: TM1.2 (S), X2.3 (VO)
unnamed: IC9.11 (CLK), IC11.12 (O)
OUT: R1.2; also elsewhere on the board
SWITCH-LED: IC6.13 (I2); also elsewhere on the board
VCC: HI.1 (LEDSUP), HI.14 (VCC), IC4.20 (VCC), IC6.14 (VCC), IC7.14 (VCC), LO.1 (LEDSUP), LO.14 (VCC), TM1.1 (A), X2.2 (VDD), X2.15 (A); also elsewhere on the board
